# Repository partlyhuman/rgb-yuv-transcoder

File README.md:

## @partlyhuman changes

The [PCB](pcb/) directory includes a fully SMD (except for the BA7230) version of the transcoder that incorporates connectors: Mini DIN-9 for RGBS input, and RCA jacks for component output.

---

# Dek's RGB-to-Component-Transcoder
A DIY RGB to Component Video Transcoder to make your own video conversion boxes. 

This schematic and associated PCB does not do any upscaling and is designed to support old CRT TVs that only have component video inputs (not RGB scart like in many european countries) and primarily as way to open up more output options for retro consoles using an external method (rather needing to directly modify the internal hardware).   

This schematic will not upscale a 240p signal. Many LCD tvs will not display a 240p picture through Component video in.

New versions (schematic, pcb files, test results etc) can be found here in the code repository
https://github.com/dekkit/RGB-to-Component-Transcoder

Versions: 
VA01  (initial prototype),
VA02  (fixes, after initial tests),   
VAxx  (future versions will be in their own folders)

If you want to want to get a bunch of PCBs manufactured - simply use the latest GERBER zip (ie Gerber_PCB_2020-04-10 17_26_57.zip) file.  Most manufacturers will provide an instant quote and typically is only be a few dollars plus postage (postage is most expensive part).   Or  use the schematic to build your own breadboard version.

Please feel free to copy, adapt and use as appropriate (public domain). If you do improve on this design, please provide an acknowledgement,  drop me a note / create an issue to let me know and share your results.

If you would like to develop your own version (customised for your specific video device, make a smaller SMD version), or simply to poke around to help further your own understanding  (pick up on any errors too!) - I used the free app EasyEDA - I've opened up the project to make it easiser to clone and adapt (see https://easyeda.com/dekkit/rgb-to-component-transcoder)

Dek.
29/5/2020

Acknowledgements to Ace, Zebidee and all variations available on the web which helped me get this far.
Also to https://www.retrorgb.com/ for most useful info on LM1881 and THS amps - it's an excellent resource highly recommended site.

FURTHER BACKGROUND

This schematic was intended to be used for consumer CRT TVs as another way to support RGB (particulary in retro video game consoles and arcade setups where crt tubes are getting harder to find/replace). It is designed to be used as an external device (outside of the system) rather be used as an internal mod.

Includes
- Audio pass through (to support the development of custom retro console cables)
- Additional variable resistors (trim pots) to attenuate incoming RGB signals and create an all-in-one style plug (useful for per retro console customisations ie snes pal).
- Composite Video to Composite Sync (to extract csync from normal composite video, in case a system does not natively output csync - like Super Nintentdo pal, or if you want to create an RGB Scart to Component transcoder) - alternatively you can also extract sync from luma or if you already have csync signal add a jumper wire.
- Mostly through-hole components to make it easier to assemble (except for the THS amp).

Design Note(s)

- Designed primarily as an external unit, input are assumed to be 75 ohm signals (hence the use of 75R resitors to ground). You may need to remove these if you intend to adapt this pcb and use it intenally.
- For arcade boards you will need to attenuate the RGB signals to a level that a normal consumer CRT will accept (ie 3-5V p-p down to 0.7V p-p) - this can be done altering the resistor values (google arcade to scart for more info and for recommended adjustments and warning -  this may damage your video hardware if not done correctly).

Materials - i've included the Bill of materials as a downloadable CSV.
- Used 1/4 watt resistors 5% (either ceramic or metallic - though many TV mods use ceramic, so use cermic if possible)
- Low voltage components are acceptable (ie I've been using 6.3v for the electrolytic cap without any issues)
- Monolythic ceramic capacitors were used (104, and 105 - again use metallic ones if ceramic is unavailable).

It has been designed to fit in a small DIY project box of dimensions 10cm x 6cm x 2.5cm (with screw holes aligned).  You can find these easily online or you can arrange a 3D print.

Initial successful testing (on version VA01 19/4/2020):
Snes (PAL), Dreamcast (NTSC), Arcade 60-in-1 Jamma PCB, Sega Saturn (PAL), Sega MegaDrive2 (PAL).

Note - on Playstation 1 (PAL) - I found this required a seperate 5v supply (as the 5v pin dropped to 3.18v underload) 

Warning
No Warranty provided /use at own risk. Will not be held liable for any damage (its free after all!).
Use quality video cables   (cheap imported video cables have all sorts of video interferences - keep cables short too!).  Also please review the issues section before building for any identified issues / work-arounds.

Please share, clone, improve and share again (pay it forward) - that way we can all benefit. 

This schematic and pcb(s) have been based on the many designs found on the web using the BA7230 chip and from plenty of own my trials and testing the outputs until i found a method and design i was comfortable with it.  Project was initiated after discovering that one of my crts was unable to be RGB modded but could be modded to support component video.

Hope you find it as useful as I have.

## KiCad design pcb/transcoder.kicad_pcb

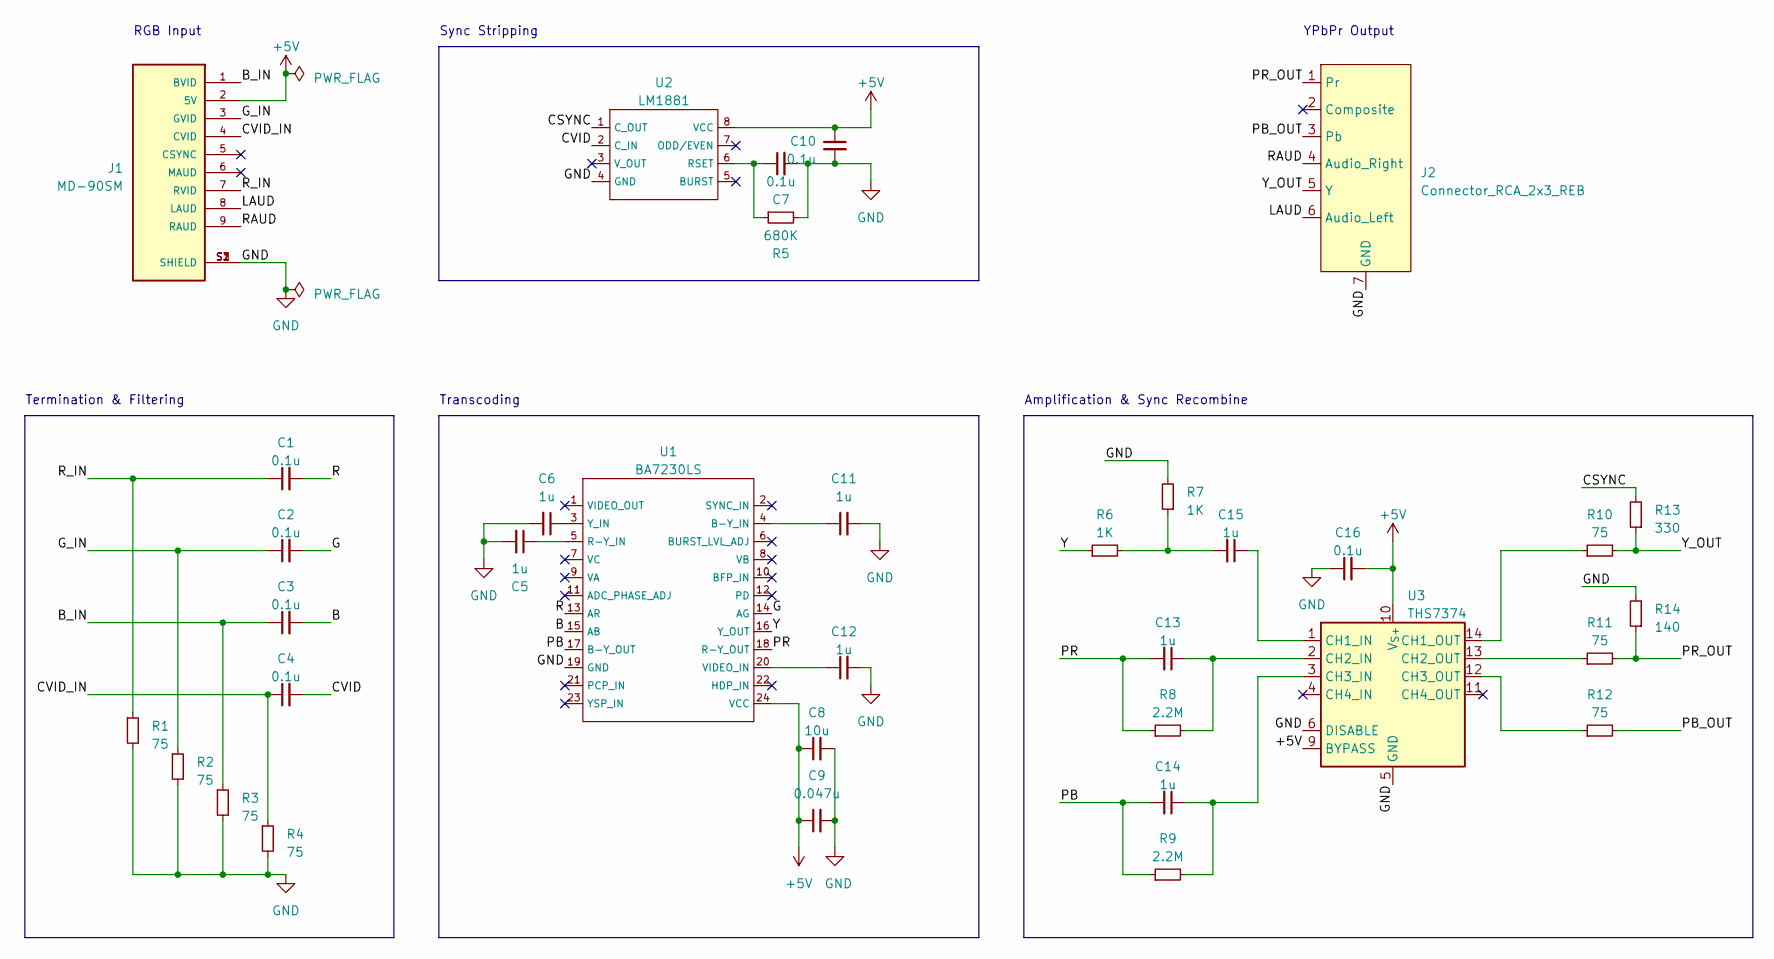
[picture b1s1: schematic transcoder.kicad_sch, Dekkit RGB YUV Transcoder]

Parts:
C1, C2, C3, C4, C7, C10, C16: 0.1u; C_0805_2012Metric_Pad1.18x1.45mm_HandSolder
C5, C6, C11, C12, C13, C14, C15: 1u; C_0805_2012Metric_Pad1.18x1.45mm_HandSolder
C8: 10u; C_0805_2012Metric_Pad1.18x1.45mm_HandSolder
C9: 0.047u; C_0805_2012Metric_Pad1.18x1.45mm_HandSolder
J1: MD-90SM; CUI_MD-90SM; PARTREV 02/18/2022
J2: Connector_RCA_2x3_REB
R1, R2, R3, R4, R10, R11, R12: 75; R_0805_2012Metric_Pad1.20x1.40mm_HandSolder
R5: 680K; R_0805_2012Metric_Pad1.20x1.40mm_HandSolder
R6, R7: 1K; R_0805_2012Metric_Pad1.20x1.40mm_HandSolder
R8, R9: 2.2M; R_0805_2012Metric_Pad1.20x1.40mm_HandSolder
R13: 330; R_0805_2012Metric_Pad1.20x1.40mm_HandSolder
R14: 140; R_0805_2012Metric_Pad1.20x1.40mm_HandSolder
U1: BA7230LS
U2: LM1881; SOIC127P599X175-8N
U3: THS7374; TSSOP-14_4.4x5mm_P0.65mm

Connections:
+5V: C8.1, C9.1, C10.1, C16.2, J1.2 (5V), U1.24 (VCC), U2.8 (VCC), U3.9 (BYPASS), U3.10 (V_{S+})
/B: C3.2, U1.15 (AB)
/B_IN: C3.1, J1.1 (BVID), R3.1
/CSYNC: R13.2, U2.1 (C_OUT)
/CVID: C4.2, U2.2 (C_IN)
/CVID_IN: C4.1, J1.4 (CVID), R4.1
/G: C2.2, U1.14 (AG)
/G_IN: C2.1, J1.3 (GVID), R2.1
/LAUD: J1.8 (LAUD), J2.6 (Audio_Left)
/PB: C14.2, R9.1, U1.17 (B-Y_OUT)
/PB_OUT: J2.3 (Pb), R12.2
/PR: C13.2, R8.1, U1.18 (R-Y_OUT)
/PR_OUT: J2.1 (Pr), R11.2, R14.1
/R: C1.2, U1.13 (AR)
/RAUD: J1.9 (RAUD), J2.4 (Audio_Right)
/R_IN: C1.1, J1.7 (RVID), R1.1
/Y: R6.1, U1.16 (Y_OUT)
/Y_OUT: J2.5 (Y), R10.2, R13.1
GND: C5.2, C6.2, C7.2, C8.2, C9.2, C10.2, C11.2, C12.2, C16.1, J1.S1 (SHIELD), J1.S2 (SHIELD), J1.S3 (SHIELD), J2.7 (GND), J2.8 (GND), J2.9 (GND), R1.2, R2.2, R3.2, R4.2, R5.2, R7.2, R14.2, U1.19 (GND), U2.4 (GND), U3.5 (GND), U3.6 (DISABLE)
unnamed: C15.2, R6.2, R7.1
unnamed: C11.1, U1.4 (B-Y_IN)
unnamed: C5.1, U1.5 (R-Y_IN)
unnamed: C12.1, U1.20 (VIDEO_IN)
unnamed: C6.1, U1.3 (Y_IN)
unnamed: C7.1, R5.1, U2.6 (RSET)
unnamed: C15.1, U3.1 (CH1_IN)
unnamed: R10.1, U3.14 (CH1_OUT)
unnamed: C13.1, R8.2, U3.2 (CH2_IN)
unnamed: R11.1, U3.13 (CH2_OUT)
unnamed: C14.1, R9.2, U3.3 (CH3_IN)
unnamed: R12.1, U3.12 (CH3_OUT)

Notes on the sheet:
RGB Input
Transcoding
Sync Stripping
YPbPr Output
Termination & Filtering
Amplification & Sync Recombine

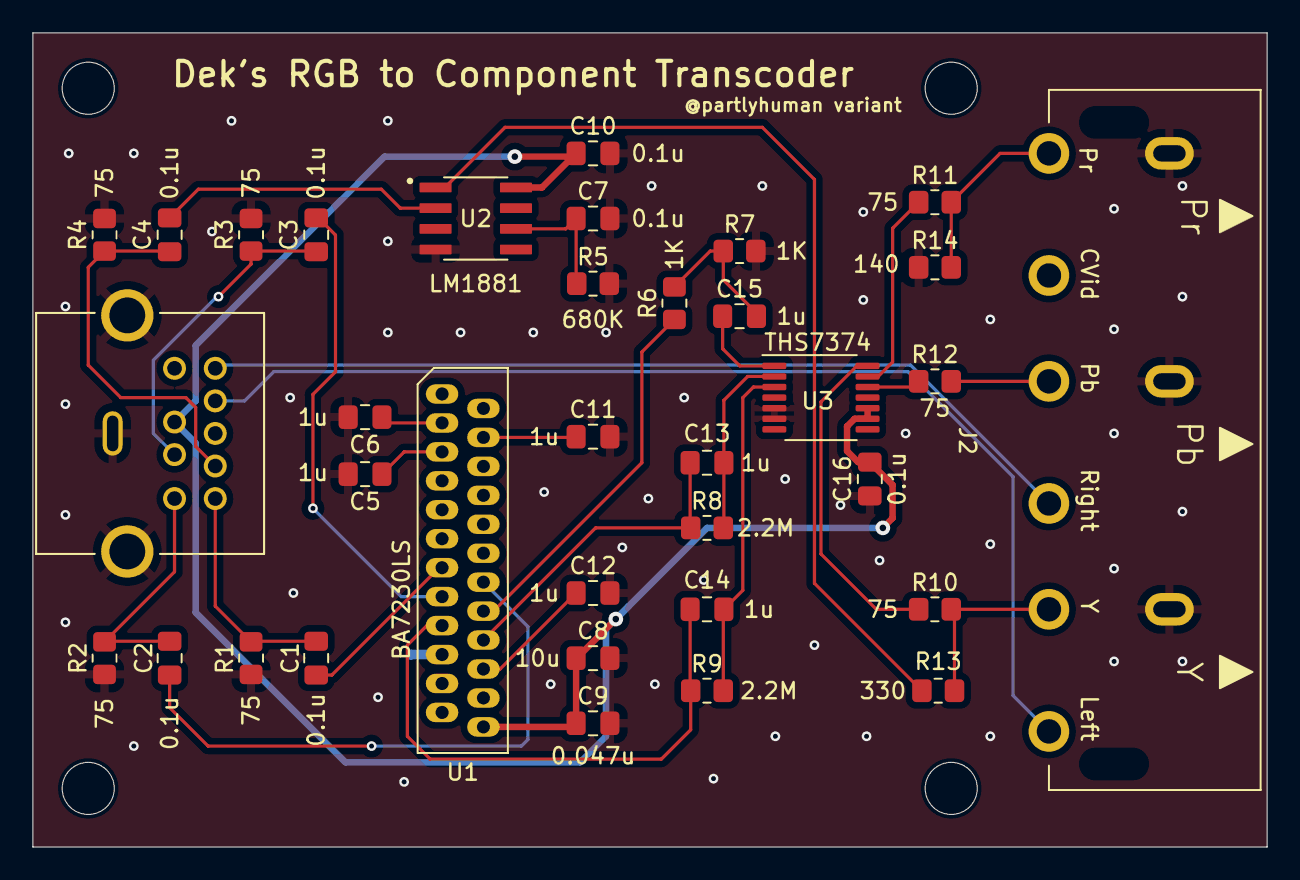
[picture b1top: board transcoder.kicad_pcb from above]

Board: 2 copper layers, 75.8 x 50.0 mm, 39 parts (0 on the bottom side), 31 nets.

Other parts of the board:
M0, M0#2, M0#3, M0#4: MountingHole_3.2mm_M3

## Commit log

2023-04-05 Interpreted VA03 schematic with DIN9 + RCA blocks
2023-04-05 Minor tweaks
2023-04-06 Mounting holes
2023-04-11 Fix ordering of filter/termination on inputs
2023-05-10 Adds silkscreens
2023-05-13 Removes stray text
2023-07-26 Notes
